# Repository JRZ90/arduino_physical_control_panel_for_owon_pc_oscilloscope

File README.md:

This is a physical control panel for owon pc oscilloscopes, but can be used with any other brand and codel. The working principle is very simple, the software has some keyboard shortcuts for control some actions such the amplitude and time scale. When you press a button or turn the knob the arduino send a signal to python and this is who send a keystroke to the oscilloscope software emulating the keyboard.

## Requirements
### Hardware
* Arduino board with USB connection, any Arduino compatible board with CH340 chip work just fine, no HID capabilities required.
* One of the pcbs for mount the components and the arduino.

### Environment
* Windows
* Python 3
* Arduino

* The PCB (ver_mini) can be easily done  with the toner transfer mnethod. But the extended version is much more complex and was designed to be done by a pcb manufacturer such as JLCPCB or PCBWAY.
* All the components are very inexpensive and easy to find. Each PCB has a Bom file with all the required components.

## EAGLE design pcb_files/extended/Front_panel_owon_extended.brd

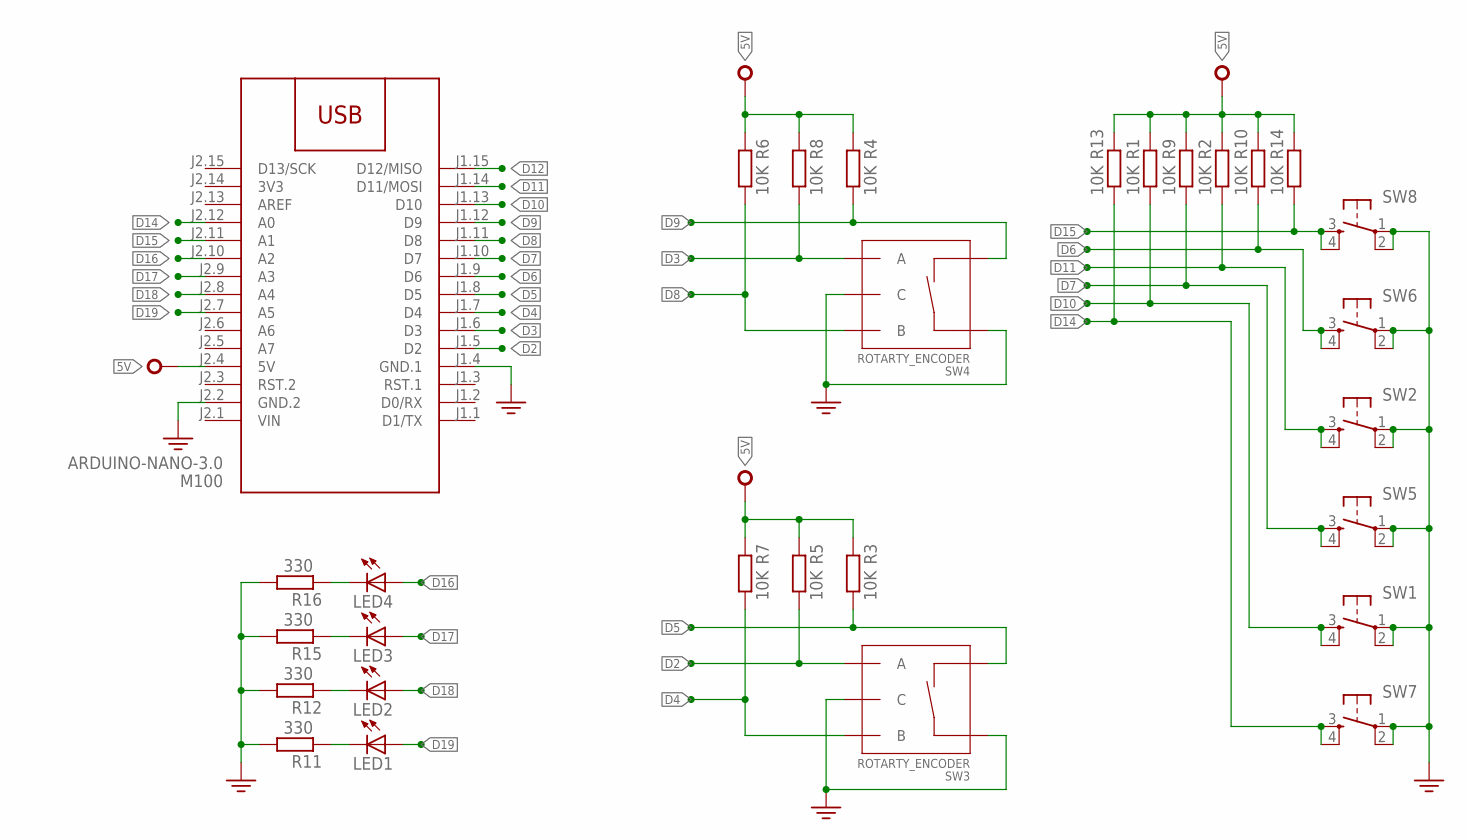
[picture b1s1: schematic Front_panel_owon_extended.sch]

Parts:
LED1, LED2, LED3, LED4: LED5MM
M100: ARDUINO-NANO-3.0
R1, R2, R3, R4, R5, R6, R7, R8, R9, R10, R13, R14: 10K; 0204/7
R11, R12, R15, R16: 330; 0204/7
SW1, SW2, SW5, SW6, SW7, SW8: TACTILE-SWITCH-PTH; TAC-SWITCH-PTH
SW3, SW4: ROTARTY_ENCODER; ROTARY_ENC_PLAIN

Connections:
3V3: M100.J2.14 (3V3)
5V: M100.J2.4 (5V), R1.2, R2.2, R3.2, R4.2, R5.2, R6.2, R7.2, R8.2, R9.2, R10.2, R13.2, R14.2
D2: M100.J1.5 (D2), R5.1, SW3.A
D3: M100.J1.6 (D3), R8.1, SW4.A
D4: M100.J1.7 (D4), R7.1, SW3.B
D5: M100.J1.8 (D5), R3.1, SW3.SW-
D6: M100.J1.9 (D6), R10.1, SW6.3, SW6.4
D7: M100.J1.10 (D7), R9.1, SW5.3, SW5.4
D8: M100.J1.11 (D8), R6.1, SW4.B
D9: M100.J1.12 (D9), R4.1, SW4.SW-
D10: M100.J1.13 (D10), R1.1, SW1.3, SW1.4
D11: M100.J1.14 (D11/MOSI), R2.1, SW2.3, SW2.4
D12: M100.J1.15 (D12/MISO)
D14: M100.J2.12 (A0), R13.1, SW7.3, SW7.4
D15: M100.J2.11 (A1), R14.1, SW8.3, SW8.4
D16: LED4.A, M100.J2.10 (A2)
D17: LED3.A, M100.J2.9 (A3)
D18: LED2.A, M100.J2.8 (A4)
D19: LED1.A, M100.J2.7 (A5)
GND: M100.J1.4 (GND.1), M100.J2.2 (GND.2), R11.2, R12.2, R15.2, R16.2, SW1.1, SW1.2, SW2.1, SW2.2, SW3.C, SW3.SW+, SW4.C, SW4.SW+, SW5.1, SW5.2, SW6.1, SW6.2, SW7.1, SW7.2, SW8.1, SW8.2
unnamed: LED1.K (C), R11.1
unnamed: LED2.K (C), R12.1
unnamed: LED3.K (C), R15.1
unnamed: LED4.K (C), R16.1
VIN: M100.J2.1 (VIN)

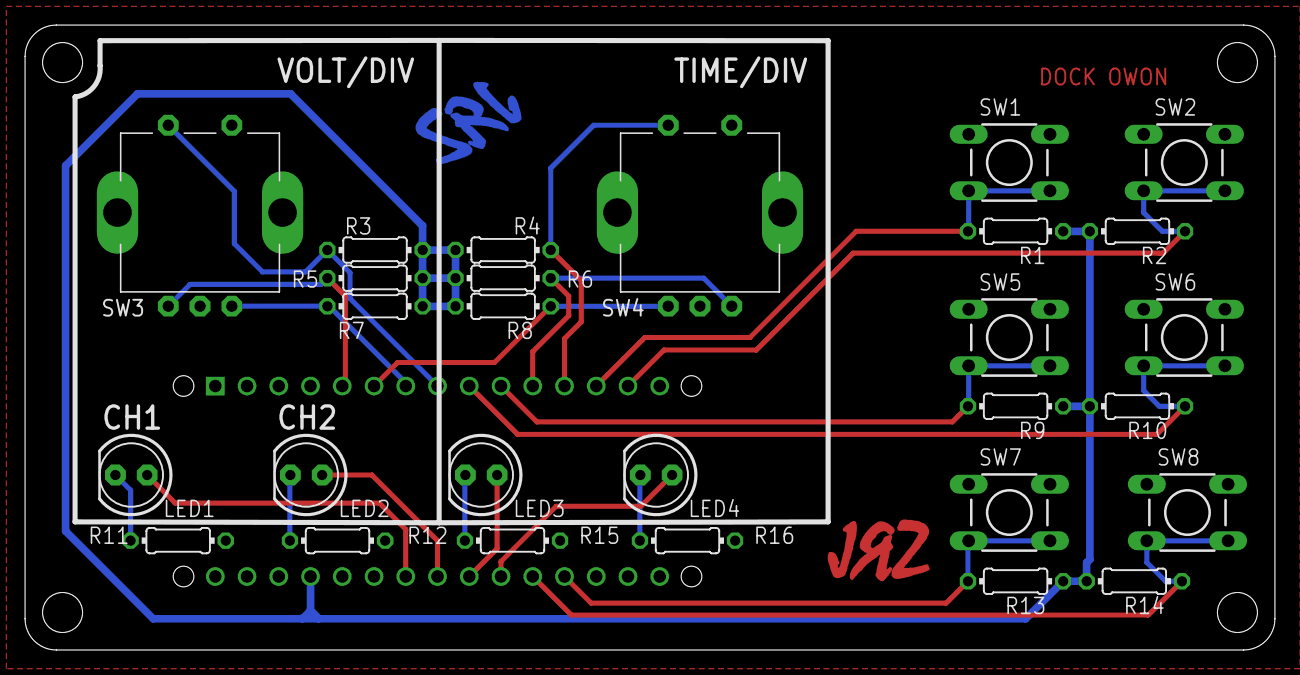
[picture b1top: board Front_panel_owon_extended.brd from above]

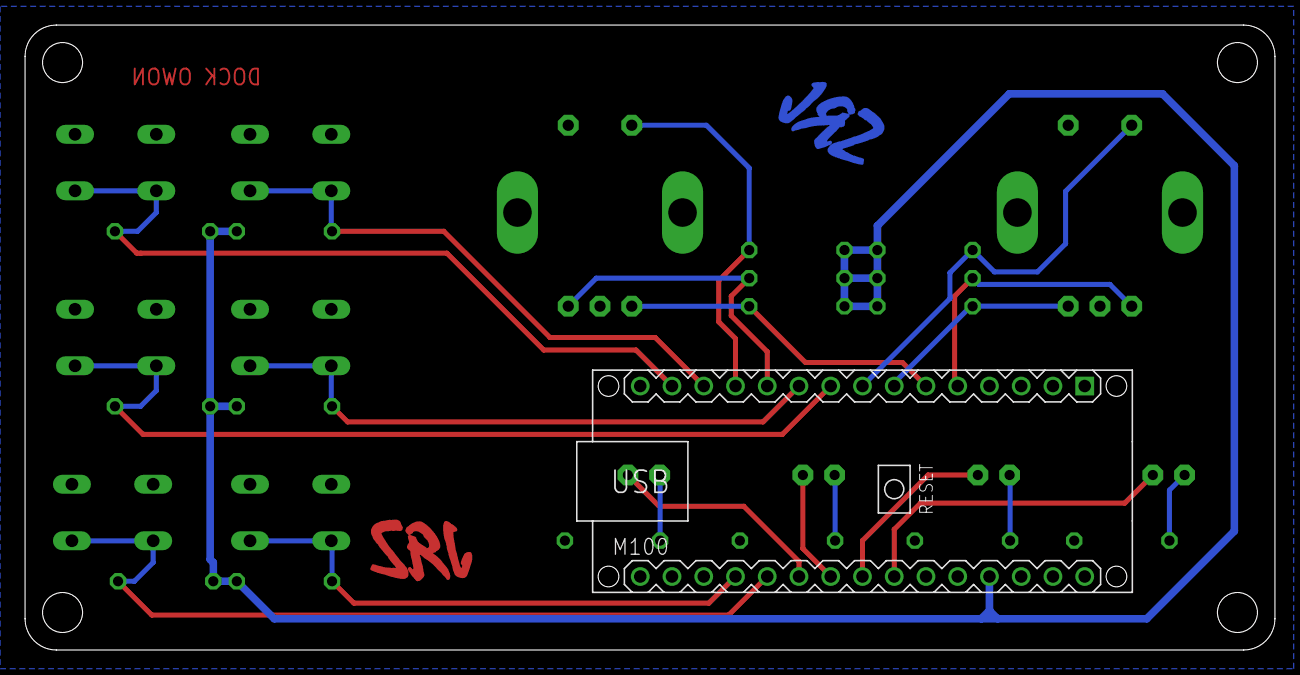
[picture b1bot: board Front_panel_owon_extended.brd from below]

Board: 2 copper layers, 100.0 x 50.0 mm, 31 parts (2 on the bottom side), 22 nets.

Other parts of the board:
U$1, U$3: LOGO_B

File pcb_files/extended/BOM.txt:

Qty 	Value              	Device             	Parts                                             		Description
4                      		LED 5mm             	LED1, LED2, LED3, LED4                            	LED                                                           
12  	10K                	RESISTOR        	R1, R2, R3, R4, R5, R6, R7, R8, R9, R10, R13, R14 	RESISTOR 1/4W
4   	330                	RESISTOR        	R11, R12, R15, R16                                		RESISTOR 1/4W
1   	ARDUINO-NANO-3.0   	ARDUINO-NANO-3.0   	M100                                              		Arduino Nano 3.0 and compatible devices                       
2   	ROTARTY_ENCODER    	ROTARTY_ENCODER    	SW3, SW4                                          		Simple no LED rotary encoder                                  
6   	TACTILE-SWITCH-PTH 	TACTILE-SWITCH-PTH 	SW1, SW2, SW5, SW6, SW7, SW8                      	Tactile Switch 4 Pins, SPST NO

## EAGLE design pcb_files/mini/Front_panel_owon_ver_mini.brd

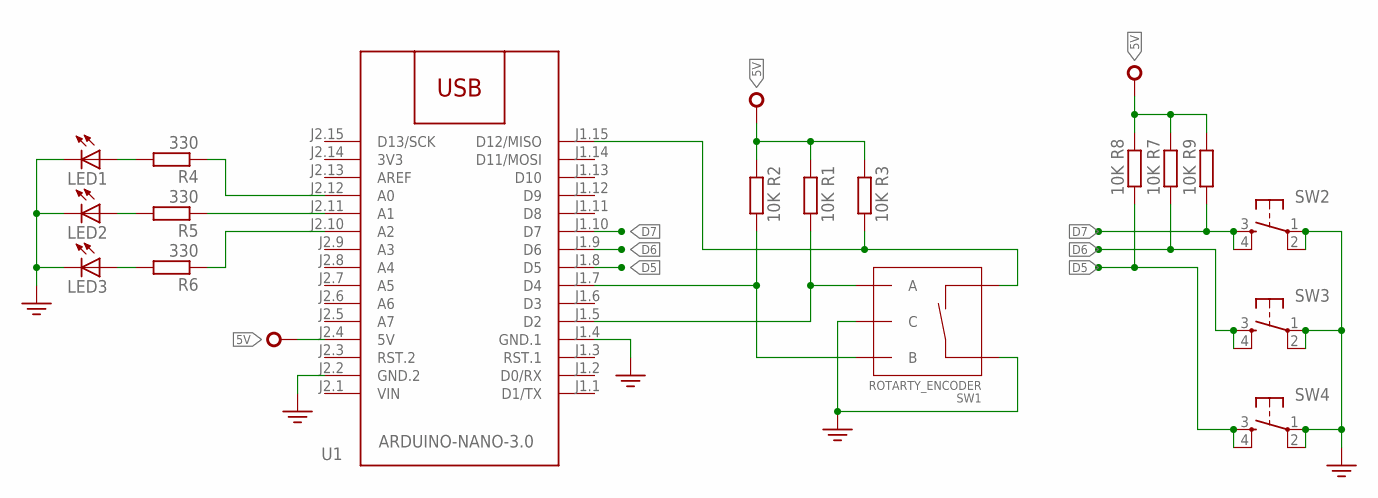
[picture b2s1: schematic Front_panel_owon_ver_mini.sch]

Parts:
LED1, LED2, LED3: LED5MM
R1, R2, R3, R7, R8, R9: 10K; 0204/7
R4, R5, R6: 330; 0204/7
SW1: ROTARTY_ENCODER; ROTARY_ENC_PLAIN
SW2, SW3, SW4: TACTILE-SWITCH-PTH; TAC-SWITCH-PTH
U1: ARDUINO-NANO-3.0

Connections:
3V3: U1.J2.14 (3V3)
5V: R1.2, R2.2, R3.2, R7.2, R8.2, R9.2, U1.J2.4 (5V)
D2: R1.1, SW1.A, U1.J1.5 (D2)
D4: R2.1, SW1.B, U1.J1.7 (D4)
D5: R8.1, SW4.3, SW4.4, U1.J1.8 (D5)
D6: R7.1, SW3.3, SW3.4, U1.J1.9 (D6)
D7: R9.1, SW2.3, SW2.4, U1.J1.10 (D7)
D12: R3.1, SW1.SW-, U1.J1.15 (D12/MISO)
GND: LED1.K (C), LED2.K (C), LED3.K (C), SW1.C, SW1.SW+, SW2.1, SW2.2, SW3.1, SW3.2, SW4.1, SW4.2, U1.J1.4 (GND.1), U1.J2.2 (GND.2)
unnamed: R5.1, U1.J2.11 (A1)
unnamed: LED1.A, R4.2
unnamed: LED2.A, R5.2
unnamed: LED3.A, R6.2
unnamed: R4.1, U1.J2.12 (A0)
unnamed: R6.1, U1.J2.10 (A2)
VIN: U1.J2.1 (VIN)

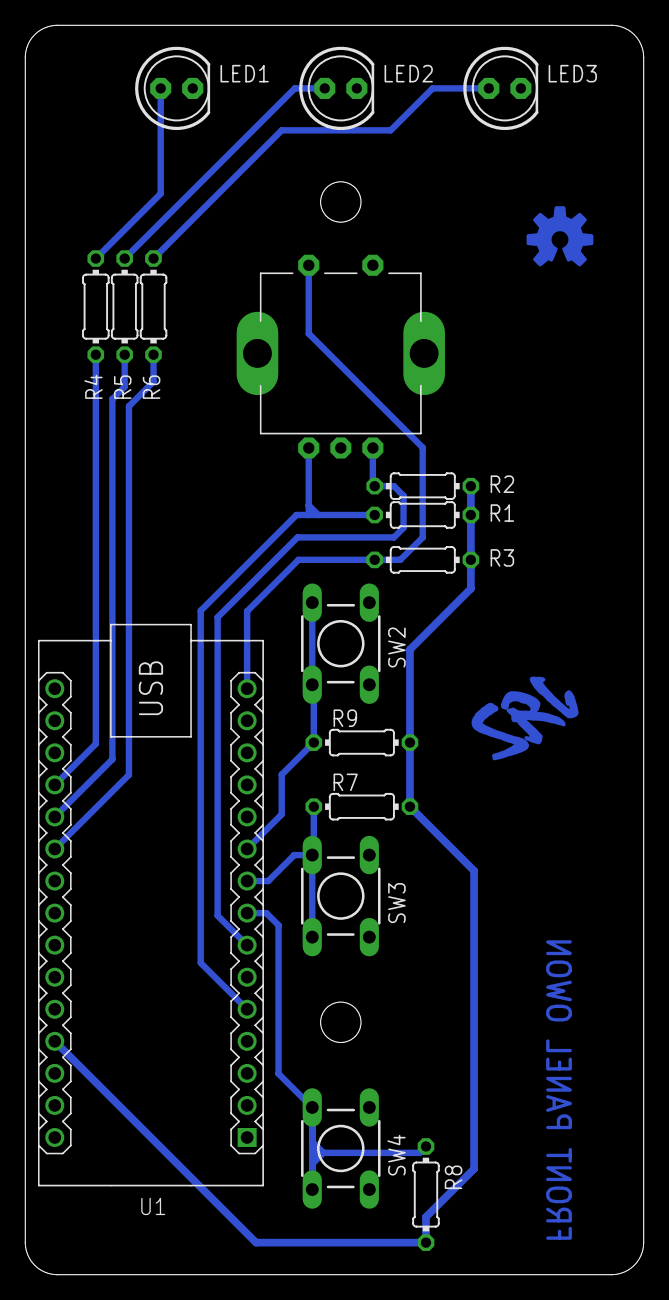
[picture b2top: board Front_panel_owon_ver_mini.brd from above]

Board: 2 copper layers, 49.0 x 99.0 mm, 20 parts (1 on the bottom side), 14 nets.

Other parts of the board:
U$1: LOGO_B
U$2: OSHWLOGO_TOP_0.2
U$3: OSHWLOGO_TOL_0.2

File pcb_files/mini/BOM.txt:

Qty 	Value              		Device             		Parts                  		Description              
3      	                		LED 5mm             		LED1, LED2, LED3       		LED                                                           
6   	10K                		RESISTOR        		R1, R2, R3, R7, R8, R9 		RESISTOR 1/4W
3   	330                		RESISTOR        		R4, R5, R6             		RESISTOR 1/4W
1   	ARDUINO-NANO-3.0   		ARDUINO-NANO-3.0   		M1                     		Arduino Nano 3.0 and compatible devices
1   	ROTARTY_ENCODER    		ROTARTY_ENCODER    		SW1                    		Simple no LED rotary encoder
3   	TACTILE-SWITCH 			TACTILE-SWITCH-PTH 		SW2, SW3, SW4          		Tactile Switch 4 Pins, SPST NO

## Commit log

2021-06-04 primer commit, todo funciona bien
2021-06-09 retoques, mejoras y agregados

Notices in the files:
parts and their libraries:
diy-modules: Released under the Creative Commons Attribution 4.0 International License: http://creativecommons.org/licenses/by/4.0
GeekAmmo: Licensing:Creative Commons ShareAlike 4.0 International - https://creativecommons.org/licenses/by-sa/4.0
